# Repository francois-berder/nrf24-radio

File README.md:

# NRF24 RC radio

This project consists of a custom board for controlling RC models using a NRF24L01+ radio.

## Hardware

The hardware consists of a custom board featuring a PIC16F1829 and a NRF24L01+ module.
The board has the following interfaces:

- 4 slots for RC servos or motor controllers
- A serial port for communication
- An ISCP port for programming the PIC16F1829

Kicad files for the custom files are present in the `hardware` directory.

### BOM

| Components      | References | Footprint        | Quantity |
| --------------- | ---------- | ---------------- | -------- |
| NRF24L01+       | U3         |                  | 1        |
| PIC16F1829      | U2         | QFN (4x4x0.9 mm) | 1        |
| MPC1700         | U1         | SOT-23           | 1        |
| Capacitor 100nF | C2         | SMD 0402         | 1        |
| Capacitor 1uF   | C1, C3     | SMD 0402         | 2        |
| Capacitor 10uF  | C4, C5     | SMD 0603         | 2        |
| Resistor 10k    | R1         | SMD 0402         | 1        |

## Firmware

The firmware is written in C and peripheral drivers were generated using MPLAB code configurator. The NRF24 driver was ported from this [repository](https://github.com/nRF24/RF24).

The device can run in 3 modes:

- RC receiver: it receives data from the radio and uses it to control servos
- RX radio: it receives data from the radio and sends it on the serial port
- TX radio: data received from the serial port is sent over the radio

### Instructions for building and flashing firmware

Requirements:

- [xc8 compiler](https://www.microchip.com/en-us/tools-resources/develop/mplab-xc-compilers)
- make

You can either build the firmware by using MPLAB X IDE or run this command:

```sh
make -C radio-firmware
```

Flash the HEX file using a [PicKit3](https://www.microchip.com/en-us/development-tool/pg164130) or a [PicKit4](https://www.microchip.com/en-us/development-tool/pg164140) by connecting the programmer to the ISCP connector present on the board.

### Configuration

The configuration of the device is stored in the PIC16F1829 EEPROM.
The size of the EEPROM is 256 bytes but only a small is currently in use.

Here is the EEPROM map:

| Address |         Description | Default value | Valid range |
| ------- | ------------------- | ------------- | ----------- |
| 0       |         Magic value |          0xDE |         N/A |
| 1       |       Radio channel |            76 |     0 - 125 |
| 2       |      Radio Datarate |   0 (250KPBS) | 0: 250KPBS, 1: 1MPBS, 2: 2MPBS |
| 3       |  Radio payload size |            32 |        1-32 |
| 4-9     | NRF24 pipe0 address |             1 |      0-2^48 |
| 10      |    Servo 0 position |           128 |     0 - 255 |
| 11      |    Servo 1 position |           128 |     0 - 255 |
| 12      |    Servo 2 position |           128 |     0 - 255 |
| 13      |    Servo 3 position |           128 |     0 - 255 |
| 14      |      Servo 0 offset |            64 |     0 - 128 |
| 15      |      Servo 1 offset |            64 |     0 - 128 |
| 16      |      Servo 2 offset |            64 |     0 - 128 |
| 17      |      Servo 3 offset |            64 |     0 - 128 |
| 18-255  |      Unused         |           N/A |         N/A |

To read and write the configuration of the device, use `scripts/config.py`.

### Serial protocol

The serial port is configured in the following way: 115200 baud, 1 stop bit, no parity bit.

Each command is one byte long followed by data.

| Command              | Value | Description | data length |
| -------------------- | ----- | ----------- | ----------- |
| WRITE_EEPROM         |     0 | Write byte to EEPROM | 2 (address and data) |
| READ_EEPROM          |     1 | Read byte from EEPROM | 1 (address) |
| REQ_FIRMWARE_VERSION |     2 | Request firmware version | 0 |
| FIRMWARE_VERSION     |     3 | Firmware version | 2 (major and minor version) |
| SERVO_ENABLE         |     4 | Send signals on servos | 0 |
| SERVO_DISABLE        |     5 | Stop signals on servos | 0 |
| EEPROM_DATA          |     6 |  Byte read from EEPROM | 1 |
| RADIO_DATA           |     7 | Data read from NRF24 radio | 32 |
| GET_MODE             |     8 | Request device mode | 0 |
| SET_MODE             |     9 | Change device mode | 1 |
| MODE                 |    10 | Current device mode | 1 |
| RESET                |    11 | Reset device | 0 |

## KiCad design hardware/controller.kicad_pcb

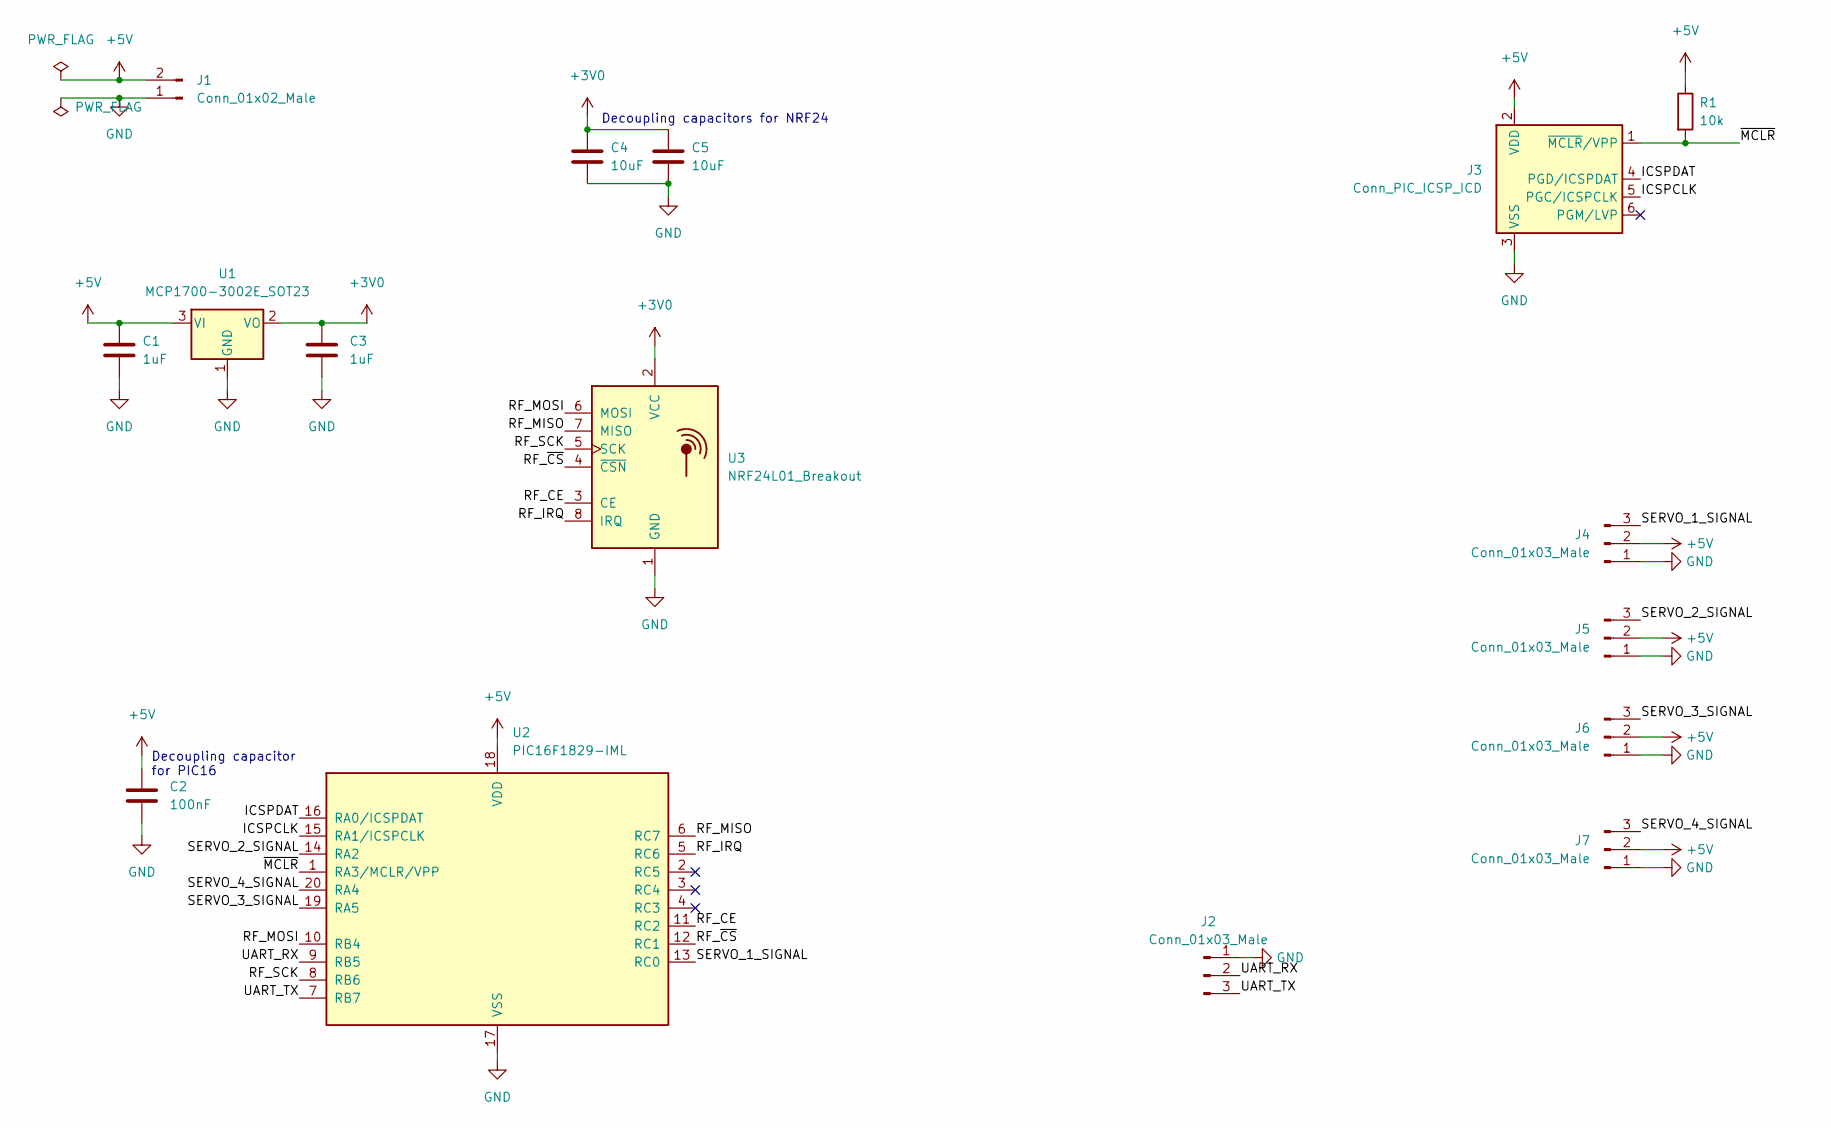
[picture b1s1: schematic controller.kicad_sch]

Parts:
C1, C3: 1uF; C_0402_1005Metric
C2: 100nF; C_0402_1005Metric
C4, C5: 10uF; C_0603_1608Metric
J1: Conn_01x02_Male
J2, J4, J5, J6, J7: Conn_01x03_Male; PinSocket_1x03_P2.54mm_Vertical
J3: Conn_PIC_ICSP_ICD; PinSocket_1x06_P2.54mm_Vertical
R1: 10k; R_0402_1005Metric
U1: MCP1700-3002E_SOT23; SOT-23
U2: PIC16F1829-IML; QFN-20-1EP_4x4mm_P0.5mm_EP2.5x2.5mm
U3: NRF24L01_Breakout; nRF24L01_Breakout

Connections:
+3V0: C3.1, C4.1, C5.1, U1.2 (VO), U3.2 (VCC)
+5V: C1.1, C2.1, J1.2, J3.2 (VDD), J4.2, J5.2, J6.2, J7.2, R1.1, U1.3 (VI), U2.18 (VDD)
/ICSPCLK: J3.5 (PGC/ICSPCLK), U2.15 (RA1/ICSPCLK)
/ICSPDAT: J3.4 (PGD/ICSPDAT), U2.16 (RA0/ICSPDAT)
/RF_CE: U2.11 (RC2), U3.3 (CE)
/RF_IRQ: U2.5 (RC6), U3.8 (IRQ)
/RF_MISO: U2.6 (RC7), U3.7 (MISO)
/RF_MOSI: U2.10 (RB4), U3.6 (MOSI)
/RF_SCK: U2.8 (RB6), U3.5 (SCK)
/RF_~CS: U2.12 (RC1), U3.4 (~CSN)
/SERVO_1_SIGNAL: J4.3, U2.13 (RC0)
/SERVO_2_SIGNAL: J5.3, U2.14 (RA2)
/SERVO_3_SIGNAL: J6.3, U2.19 (RA5)
/SERVO_4_SIGNAL: J7.3, U2.20 (RA4)
/UART_RX: J2.2, U2.9 (RB5)
/UART_TX: J2.3, U2.7 (RB7)
/~MCLR: J3.1 (~MCLR/VPP), R1.2, U2.1 (RA3/MCLR/VPP)
GND: C1.2, C2.2, C3.2, C4.2, C5.2, J1.1, J2.1, J3.3 (VSS), J4.1, J5.1, J6.1, J7.1, U1.1 (GND), U2.17 (VSS), U3.1 (GND)

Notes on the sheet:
Decoupling capacitor for PIC16
Decoupling capacitors for NRF24

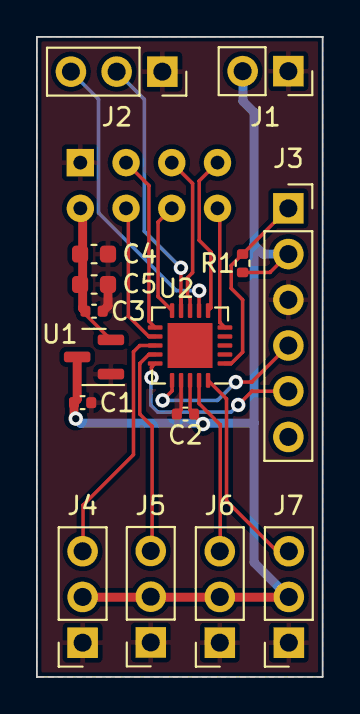
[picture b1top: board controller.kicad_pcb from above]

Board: 2 copper layers, 15.9 x 35.6 mm, 16 parts (1 on the bottom side), 18 nets.

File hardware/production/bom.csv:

Designator,Footprint,Quantity,Value,LCSC Part #
"C1, C3",402,2,"1uF, X7R",
C2,402,1,"100nF, X7R",
"C4, C5",603,2,"10uF, X7R",
J1,PinSocket_1x02_P2.54mm_Vertical,1,Conn_01x02_Female,
"J2, J4, J5, J6, J7",PinSocket_1x03_P2.54mm_Vertical,5,Conn_01x03_Male,
J3,PinSocket_1x06_P2.54mm_Vertical,1,Conn_PIC_ICSP_ICD,
R1,402,1,10k,
U1,SOT-23,1,MCP1700-3002E_SOT23,
U2,QFN-20-1EP_4x4mm_P0.5mm_EP2.5x2.5mm,1,PIC16F1829-IML,

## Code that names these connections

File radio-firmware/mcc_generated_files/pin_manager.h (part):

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// get/set SERVO_2_SIGNAL aliases
#define SERVO_2_SIGNAL_TRIS                 TRISAbits.TRISA2
#define SERVO_2_SIGNAL_LAT                  LATAbits.LATA2
#define SERVO_2_SIGNAL_PORT                 PORTAbits.RA2
#define SERVO_2_SIGNAL_WPU                  WPUAbits.WPUA2
#define SERVO_2_SIGNAL_ANS                  ANSELAbits.ANSA2
#define SERVO_2_SIGNAL_SetHigh()            do { LATAbits.LATA2 = 1; } while(0)
#define SERVO_2_SIGNAL_SetLow()             do { LATAbits.LATA2 = 0; } while(0)
#define SERVO_2_SIGNAL_Toggle()             do { LATAbits.LATA2 = ~LATAbits.LATA2; } while(0)
#define SERVO_2_SIGNAL_GetValue()           PORTAbits.RA2
#define SERVO_2_SIGNAL_SetDigitalInput()    do { TRISAbits.TRISA2 = 1; } while(0)
#define SERVO_2_SIGNAL_SetDigitalOutput()   do { TRISAbits.TRISA2 = 0; } while(0)
#define SERVO_2_SIGNAL_SetPullup()          do { WPUAbits.WPUA2 = 1; } while(0)
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// get/set SERVO_4_SIGNAL aliases
#define SERVO_4_SIGNAL_TRIS                 TRISAbits.TRISA4
#define SERVO_4_SIGNAL_LAT                  LATAbits.LATA4
#define SERVO_4_SIGNAL_PORT                 PORTAbits.RA4
#define SERVO_4_SIGNAL_WPU                  WPUAbits.WPUA4
#define SERVO_4_SIGNAL_ANS                  ANSELAbits.ANSA4
#define SERVO_4_SIGNAL_SetHigh()            do { LATAbits.LATA4 = 1; } while(0)
#define SERVO_4_SIGNAL_SetLow()             do { LATAbits.LATA4 = 0; } while(0)
#define SERVO_4_SIGNAL_Toggle()             do { LATAbits.LATA4 = ~LATAbits.LATA4; } while(0)
#define SERVO_4_SIGNAL_GetValue()           PORTAbits.RA4
#define SERVO_4_SIGNAL_SetDigitalInput()    do { TRISAbits.TRISA4 = 1; } while(0)
#define SERVO_4_SIGNAL_SetDigitalOutput()   do { TRISAbits.TRISA4 = 0; } while(0)
#define SERVO_4_SIGNAL_SetPullup()          do { WPUAbits.WPUA4 = 1; } while(0)
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// get/set SERVO_3_SIGNAL aliases
#define SERVO_3_SIGNAL_TRIS                 TRISAbits.TRISA5
#define SERVO_3_SIGNAL_LAT                  LATAbits.LATA5
#define SERVO_3_SIGNAL_PORT                 PORTAbits.RA5
#define SERVO_3_SIGNAL_WPU                  WPUAbits.WPUA5
#define SERVO_3_SIGNAL_SetHigh()            do { LATAbits.LATA5 = 1; } while(0)
#define SERVO_3_SIGNAL_SetLow()             do { LATAbits.LATA5 = 0; } while(0)
#define SERVO_3_SIGNAL_Toggle()             do { LATAbits.LATA5 = ~LATAbits.LATA5; } while(0)
#define SERVO_3_SIGNAL_GetValue()           PORTAbits.RA5
#define SERVO_3_SIGNAL_SetDigitalInput()    do { TRISAbits.TRISA5 = 1; } while(0)
#define SERVO_3_SIGNAL_SetDigitalOutput()   do { TRISAbits.TRISA5 = 0; } while(0)
#define SERVO_3_SIGNAL_SetPullup()          do { WPUAbits.WPUA5 = 1; } while(0)
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// get/set SOFTSPI_MOSI_IO aliases
#define SOFTSPI_MOSI_IO_TRIS                 TRISBbits.TRISB4
#define SOFTSPI_MOSI_IO_LAT                  LATBbits.LATB4
#define SOFTSPI_MOSI_IO_PORT                 PORTBbits.RB4
#define SOFTSPI_MOSI_IO_WPU                  WPUBbits.WPUB4
#define SOFTSPI_MOSI_IO_ANS                  ANSELBbits.ANSB4
#define SOFTSPI_MOSI_IO_SetHigh()            do { LATBbits.LATB4 = 1; } while(0)
#define SOFTSPI_MOSI_IO_SetLow()             do { LATBbits.LATB4 = 0; } while(0)
#define SOFTSPI_MOSI_IO_Toggle()             do { LATBbits.LATB4 = ~LATBbits.LATB4; } while(0)
#define SOFTSPI_MOSI_IO_GetValue()           PORTBbits.RB4
#define SOFTSPI_MOSI_IO_SetDigitalInput()    do { TRISBbits.TRISB4 = 1; } while(0)
#define SOFTSPI_MOSI_IO_SetDigitalOutput()   do { TRISBbits.TRISB4 = 0; } while(0)
#define SOFTSPI_MOSI_IO_SetPullup()          do { WPUBbits.WPUB4 = 1; } while(0)
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#define RB5_SetHigh()            do { LATBbits.LATB5 = 1; } while(0)
#define RB5_SetLow()             do { LATBbits.LATB5 = 0; } while(0)
#define RB5_Toggle()             do { LATBbits.LATB5 = ~LATBbits.LATB5; } while(0)
#define RB5_GetValue()              PORTBbits.RB5
#define RB5_SetDigitalInput()    do { TRISBbits.TRISB5 = 1; } while(0)
#define RB5_SetDigitalOutput()   do { TRISBbits.TRISB5 = 0; } while(0)
#define RB5_SetPullup()             do { WPUBbits.WPUB5 = 1; } while(0)
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// get/set SOFTSPI_SCK_IO aliases
#define SOFTSPI_SCK_IO_TRIS                 TRISBbits.TRISB6
#define SOFTSPI_SCK_IO_LAT                  LATBbits.LATB6
#define SOFTSPI_SCK_IO_PORT                 PORTBbits.RB6
#define SOFTSPI_SCK_IO_WPU                  WPUBbits.WPUB6
#define SOFTSPI_SCK_IO_SetHigh()            do { LATBbits.LATB6 = 1; } while(0)
#define SOFTSPI_SCK_IO_SetLow()             do { LATBbits.LATB6 = 0; } while(0)
#define SOFTSPI_SCK_IO_Toggle()             do { LATBbits.LATB6 = ~LATBbits.LATB6; } while(0)
#define SOFTSPI_SCK_IO_GetValue()           PORTBbits.RB6
#define SOFTSPI_SCK_IO_SetDigitalInput()    do { TRISBbits.TRISB6 = 1; } while(0)
#define SOFTSPI_SCK_IO_SetDigitalOutput()   do { TRISBbits.TRISB6 = 0; } while(0)
#define SOFTSPI_SCK_IO_SetPullup()          do { WPUBbits.WPUB6 = 1; } while(0)
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#define RB7_SetHigh()            do { LATBbits.LATB7 = 1; } while(0)
#define RB7_SetLow()             do { LATBbits.LATB7 = 0; } while(0)
#define RB7_Toggle()             do { LATBbits.LATB7 = ~LATBbits.LATB7; } while(0)
#define RB7_GetValue()              PORTBbits.RB7
#define RB7_SetDigitalInput()    do { TRISBbits.TRISB7 = 1; } while(0)
#define RB7_SetDigitalOutput()   do { TRISBbits.TRISB7 = 0; } while(0)
#define RB7_SetPullup()             do { WPUBbits.WPUB7 = 1; } while(0)
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// get/set SERVO_1_SIGNAL aliases
#define SERVO_1_SIGNAL_TRIS                 TRISCbits.TRISC0
#define SERVO_1_SIGNAL_LAT                  LATCbits.LATC0
#define SERVO_1_SIGNAL_PORT                 PORTCbits.RC0
#define SERVO_1_SIGNAL_WPU                  WPUCbits.WPUC0
#define SERVO_1_SIGNAL_ANS                  ANSELCbits.ANSC0
#define SERVO_1_SIGNAL_SetHigh()            do { LATCbits.LATC0 = 1; } while(0)
#define SERVO_1_SIGNAL_SetLow()             do { LATCbits.LATC0 = 0; } while(0)
#define SERVO_1_SIGNAL_Toggle()             do { LATCbits.LATC0 = ~LATCbits.LATC0; } while(0)
#define SERVO_1_SIGNAL_GetValue()           PORTCbits.RC0
#define SERVO_1_SIGNAL_SetDigitalInput()    do { TRISCbits.TRISC0 = 1; } while(0)
#define SERVO_1_SIGNAL_SetDigitalOutput()   do { TRISCbits.TRISC0 = 0; } while(0)
#define SERVO_1_SIGNAL_SetPullup()          do { WPUCbits.WPUC0 = 1; } while(0)
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// get/set RF_CS_IO aliases
#define RF_CS_IO_TRIS                 TRISCbits.TRISC1
#define RF_CS_IO_LAT                  LATCbits.LATC1
#define RF_CS_IO_PORT                 PORTCbits.RC1
#define RF_CS_IO_WPU                  WPUCbits.WPUC1
#define RF_CS_IO_ANS                  ANSELCbits.ANSC1
#define RF_CS_IO_SetHigh()            do { LATCbits.LATC1 = 1; } while(0)
#define RF_CS_IO_SetLow()             do { LATCbits.LATC1 = 0; } while(0)
#define RF_CS_IO_Toggle()             do { LATCbits.LATC1 = ~LATCbits.LATC1; } while(0)
#define RF_CS_IO_GetValue()           PORTCbits.RC1
#define RF_CS_IO_SetDigitalInput()    do { TRISCbits.TRISC1 = 1; } while(0)
#define RF_CS_IO_SetDigitalOutput()   do { TRISCbits.TRISC1 = 0; } while(0)
#define RF_CS_IO_SetPullup()          do { WPUCbits.WPUC1 = 1; } while(0)
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// get/set RF_CE_IO aliases
#define RF_CE_IO_TRIS                 TRISCbits.TRISC2
#define RF_CE_IO_LAT                  LATCbits.LATC2
#define RF_CE_IO_PORT                 PORTCbits.RC2
#define RF_CE_IO_WPU                  WPUCbits.WPUC2
#define RF_CE_IO_ANS                  ANSELCbits.ANSC2
#define RF_CE_IO_SetHigh()            do { LATCbits.LATC2 = 1; } while(0)
#define RF_CE_IO_SetLow()             do { LATCbits.LATC2 = 0; } while(0)
#define RF_CE_IO_Toggle()             do { LATCbits.LATC2 = ~LATCbits.LATC2; } while(0)
#define RF_CE_IO_GetValue()           PORTCbits.RC2
#define RF_CE_IO_SetDigitalInput()    do { TRISCbits.TRISC2 = 1; } while(0)
#define RF_CE_IO_SetDigitalOutput()   do { TRISCbits.TRISC2 = 0; } while(0)
#define RF_CE_IO_SetPullup()          do { WPUCbits.WPUC2 = 1; } while(0)
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// get/set RF_IRQ aliases
#define RF_IRQ_TRIS                 TRISCbits.TRISC6
#define RF_IRQ_LAT                  LATCbits.LATC6
#define RF_IRQ_PORT                 PORTCbits.RC6
#define RF_IRQ_WPU                  WPUCbits.WPUC6
#define RF_IRQ_ANS                  ANSELCbits.ANSC6
#define RF_IRQ_SetHigh()            do { LATCbits.LATC6 = 1; } while(0)
#define RF_IRQ_SetLow()             do { LATCbits.LATC6 = 0; } while(0)
#define RF_IRQ_Toggle()             do { LATCbits.LATC6 = ~LATCbits.LATC6; } while(0)
#define RF_IRQ_GetValue()           PORTCbits.RC6
#define RF_IRQ_SetDigitalInput()    do { TRISCbits.TRISC6 = 1; } while(0)
#define RF_IRQ_SetDigitalOutput()   do { TRISCbits.TRISC6 = 0; } while(0)
#define RF_IRQ_SetPullup()          do { WPUCbits.WPUC6 = 1; } while(0)
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// get/set SOFTSPI_MISO_IO aliases
#define SOFTSPI_MISO_IO_TRIS                 TRISCbits.TRISC7
#define SOFTSPI_MISO_IO_LAT                  LATCbits.LATC7
#define SOFTSPI_MISO_IO_PORT                 PORTCbits.RC7
#define SOFTSPI_MISO_IO_WPU                  WPUCbits.WPUC7
#define SOFTSPI_MISO_IO_ANS                  ANSELCbits.ANSC7
#define SOFTSPI_MISO_IO_SetHigh()            do { LATCbits.LATC7 = 1; } while(0)
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
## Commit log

2024-08-05 Initial import

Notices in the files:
radio-firmware/mcc_generated_files/pin_manager.h:
(c) 2018 Microchip Technology Inc. and its subsidiaries.
